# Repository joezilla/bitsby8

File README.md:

# BitsBy8

**BitsBy8** turns a Raspberry Pi (or any Linux/macOS machine) into a disk server and virtual-machine workbench for the **MITS Altair 8800** and other **S-100** computers.

It serves virtual floppy and hard-disk images to a real Altair through its **FDC+ Enhanced Floppy Disk Controller** over a serial cable — and it can also build and boot fully **virtual S-100 machines** right in your browser, no hardware required. Everything runs from a single Svelte web UI, with a REST API and an MCP server for AI assistants on the side.

**Version:** 3.0.0-alpha · **License:** GPL-3.0 · **Platforms:** Linux (Raspberry Pi & x86), macOS

---

## What it does

**Serve disks to a real Altair.** Mount up to four floppies (plus larger hard-disk images) and serve them to an unmodified Altair 8800 through its FDC+ controller over serial — or over a WebSocket link to an Altair *simulator*. Drives can be read-only or copy-on-write, and multiple machines can share the same library at once.

**Run virtual machines.** Assemble an S-100 computer from a catalog of emulated cards — CPU (8080/Z80), RAM, disk, serial, video — save it as a reusable **Machine Profile**, and boot it in the browser. Each running machine gets a live serial console, an Altair-style **front panel**, and a **video monitor** (VDM-1 character display / Cromemco Dazzler graphics). Snapshot a machine and restore it later.

**One place to drive it all.** The web UI, a full REST API, and an MCP server (90+ tools) all reach the same live state, so you can operate BitsBy8 by hand, from scripts, or from an AI assistant.

At a glance:

- 💾 **Disk serving** over real serial or WebSocket, with read-only and copy-on-write (transient / per-client "splinter") mounts you can keep, commit, or save as a new image
- 🖥️ **Virtual S-100 machines** — card catalog, machine profiles, and a run cockpit with console, front panel, and video monitor
- ⌨️ **VT102 terminal** in the browser for a real serial console or a virtual machine's console — reconnects where you left off
- 🧑‍🤝‍🧑 **Multi-client serving** so several machines (real and virtual) share one disk library
- 📼 **Cassette audio** playback
- 🤖 **AI assistant integration** via MCP (stdio or HTTP), plus OpenAPI/Swagger docs at `/api/docs`

---

## Quick start (no hardware needed)

Try the whole thing on your laptop — mount a sample disk or boot a virtual machine without an Altair in sight:

```bash
git clone <repo-url> fdcplus-web && cd fdcplus-web
pnpm install            # provisions the backend + frontend workspace
pnpm dev:all            # backend + web UI, live-reloading
open http://localhost:3000
```

Requires **Node.js 22+** and **pnpm**.

---

## Installation

### Raspberry Pi / Debian (recommended for real hardware)

Build and install the `.deb`, then run it as a systemd service:

```bash
make deb
sudo dpkg -i ../bitsby8_*.deb
sudo apt-get install -f            # pull in any missing dependencies

sudo nano /etc/bitsby8/bitsby8.config.json   # set your serial port, drives, etc.
sudo systemctl enable --now bitsby8          # start on boot and now
```

Upgrading from an older `fdcsds` install is automatic — apt supersedes it and
your config, data, and database are migrated. 

The web UI is then at `http://<pi-hostname>:3000`. See [DEBIAN-PACKAGE.md](DEBIAN-PACKAGE.md) for the full packaging guide.

### Docker

```bash
docker compose up -d      # then open the web UI (default port 3000)
```

Configuration and data persist in the mounted volume; see [`docker-compose.yml`](docker-compose.yml).

### From source

```bash
git clone <repo-url> fdcplus-web && cd fdcplus-web
pnpm install
pnpm build:all            # compile backend + build the web UI
pnpm start -- --web       # or: bitsby8 --web  (if installed globally)
```

---

## Connecting a real Altair

Wire the FDC+ controller to a USB serial adapter and point BitsBy8 at that port:

```bash
bitsby8 -p /dev/ttyUSB0 -0 disks/cpm22.dsk -w
# -p  serial port for the FDC+     -0..-3  mount a disk to a drive
# -w  enable the web interface     -b <rate>  set baud (default 230400)
```

A second serial port can drive an interactive **console terminal** in the web UI:

```bash
bitsby8 -p /dev/ttyUSB0 -0 disks/cpm22.dsk \
  --terminal-port /dev/ttyUSB1 --terminal-baud 9600 -w
```

A few setup notes:

- **Serial permissions (Linux):** add your user to the `dialout` group (`sudo usermod -aG dialout $USER`, then log out and back in).
- **Stable port names:** USB port names like `/dev/ttyUSB0` can shuffle across reboots. Run `bitsby8 --show-persistent-paths` to get a stable `/dev/serial/by-id/...` path for your config.
- **No physical FDC+?** An Altair *simulator* can connect over WebSocket instead of serial — see [docs/WS-FDC-TRANSPORT.md](docs/WS-FDC-TRANSPORT.md).

Generate a starter config any time with `bitsby8 --example-config > .bitsby8.config`, and run `bitsby8 --help` for the full option list.

---

## The web interface

Open the UI and everything is in the left sidebar:

| Section | What it's for |
|---|---|
| **Disks** | Mount/unmount images across the four drive bays, toggle read-only, browse and upload the disk library, take snapshots |
| **Virtual Machines** | Boot machine profiles and drive them in the run cockpit — serial console, Altair front panel, video monitor |
| **Card Catalog** / **Machine Profiles** | Assemble S-100 machines from emulated cards and save them as reusable profiles |
| **Terminal** | A VT102 console for a real serial port or a running virtual machine |
| **Cassettes** | Play cassette-tape audio images |
| **Disk Clients** | See and manage the machines currently sharing your disks (multi-client serving) |
| **Scripts** | Replay canned input / XMODEM transfers to a machine |
| **Config** | Server settings — serial defaults, web/API, MCP |

More detail in [docs/WEB-INTERFACE.md](docs/WEB-INTERFACE.md).

---

## AI assistant integration (MCP)

BitsBy8 ships a [Model Context Protocol](https://modelcontextprotocol.io/) server exposing 90+ tools — mount disks, drive machines, read/write CP/M files, run the terminal — to assistants like Claude Code. It's **off by default**; opt in per transport:

- **Local (stdio):** point your assistant at `bitsby8 --mcp`:
  ```json
  { "mcpServers": { "bitsby8": { "command": "bitsby8", "args": ["--mcp", "--data-dir", "/path/to/data"] } } }
  ```
- **Over the LAN (HTTP):** set an API key, then enable MCP-over-HTTP in *Config → MCP server* (or `--mcp-http`). It requires a bearer token and is intended for trusted networks — put TLS in front if you expose it.

The tools can read and **write** disk images and send bytes to real hardware, so don't point an assistant at a production machine without meaning to.

---

## Configuration

Settings live at two layers:

- **Install-time defaults** — a config file (`/etc/bitsby8/bitsby8.config.json`, or `.bitsby8.config` from source) plus CLI flags. These set up the box; changes take effect on restart.
- **Day-to-day settings** — managed live from the web UI (and REST/MCP), stored in a SQLite database in the data directory. Per-image settings like notes, write policy, and snapshots live here and apply immediately.

The data directory (`/var/lib/bitsby8` on a `.deb` install) holds your disk library, uploads, cassettes, and the database.

---

## Documentation

- [DEBIAN-PACKAGE.md](DEBIAN-PACKAGE.md) — building and installing the Debian package
- [docs/WEB-INTERFACE.md](docs/WEB-INTERFACE.md) — web UI walkthrough
- [docs/WS-FDC-TRANSPORT.md](docs/WS-FDC-TRANSPORT.md) — WebSocket disk transport for simulators
- [docs/PROTOCOL.md](docs/PROTOCOL.md) — the FDC+ serial disk protocol
- [docs/TROUBLESHOOTING.md](docs/TROUBLESHOOTING.md) — common issues
- [CONTRIBUTING.md](CONTRIBUTING.md) — how to contribute

---

## License

GPL-3.0.

## Credits

- **BitsBy8 software** (disk server, web interface, virtual machines, MCP server): Joe Toppe, 2024–present.
- **FDC+ Enhanced Floppy Disk Controller hardware:** Mike Douglas / [deramp.com](http://www.deramp.com). BitsBy8 talks to that controller over serial; the hardware itself is a separate product.

See [AUTHORS](AUTHORS) for the full contributor list.

## References

- [FDC+ Hardware Documentation](http://www.deramp.com)
- [Altair 8800 (Wikipedia)](https://en.wikipedia.org/wiki/Altair_8800)
- [Node.js SerialPort](https://serialport.io/)

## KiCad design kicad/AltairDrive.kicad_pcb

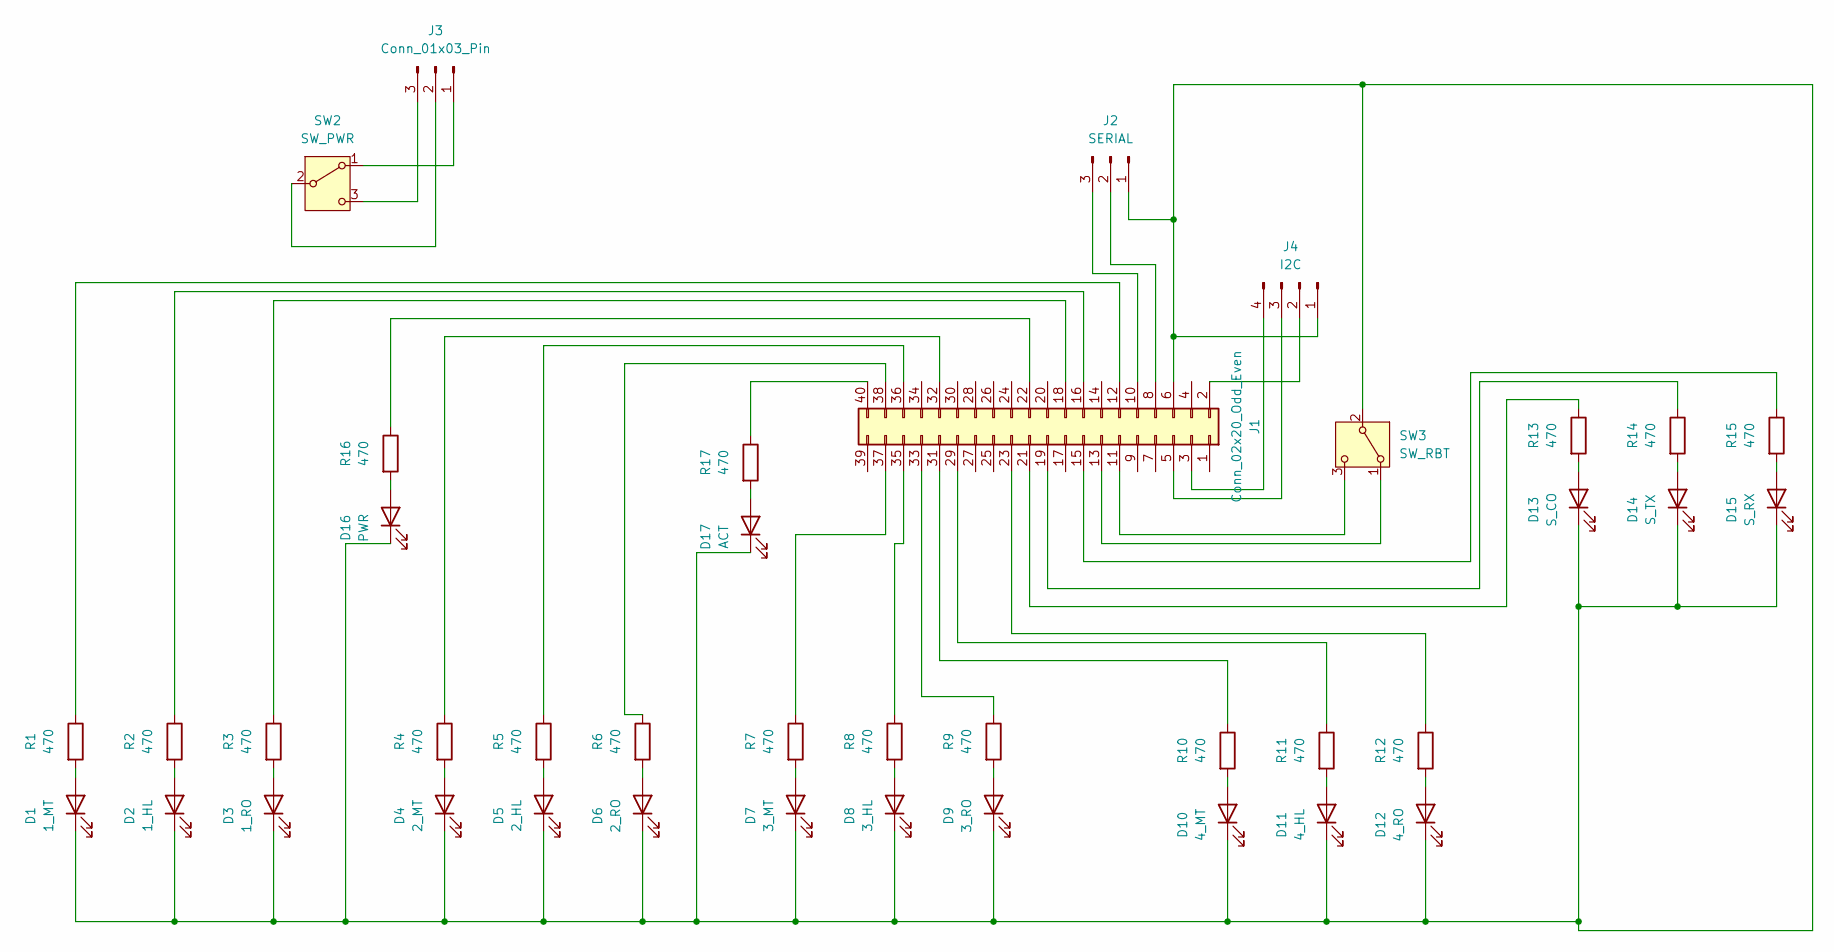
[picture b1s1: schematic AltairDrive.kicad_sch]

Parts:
D1: 1_MT; LED_D5.0mm
D2: 1_HL; LED_D5.0mm
D3: 1_RO; LED_D5.0mm
D4: 2_MT; LED_D5.0mm
D5: 2_HL; LED_D5.0mm
D6: 2_RO; LED_D5.0mm
D7: 3_MT; LED_D5.0mm
D8: 3_HL; LED_D5.0mm
D9: 3_RO; LED_D5.0mm
D10: 4_MT; LED_D5.0mm
D11: 4_HL; LED_D5.0mm
D12: 4_RO; LED_D5.0mm
D13: S_CO; LED_D5.0mm
D14: S_TX; LED_D5.0mm
D15: S_RX; LED_D5.0mm
D16: PWR; LED_D5.0mm
D17: ACT; LED_D5.0mm
J1: Conn_02x20_Odd_Even; PinHeader_2x20_P2.54mm_Vertical
J2: SERIAL; FanPinHeader_1x03_P2.54mm_Vertical
J3: Conn_01x03_Pin; FanPinHeader_1x03_P2.54mm_Vertical
J4: I2C; FanPinHeader_1x04_P2.54mm_Vertical
R1, R2, R3, R4, R5, R6, R7, R8, R9, R10, R11, R12, R13, R14, R15, R16, R17: 470; R_Bare_Metal_Element_L12.4mm_W4.8mm_P11.40mm
SW2: SW_PWR; E-Switch
SW3: SW_RBT; E-Switch

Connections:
unnamed: D1.2 (A), R1.2
unnamed: D1.1 (K), D2.1 (K), D3.1 (K), D4.1 (K), D5.1 (K), D6.1 (K), D7.1 (K), D8.1 (K), D9.1 (K), D10.1 (K), D11.1 (K), D12.1 (K), D13.1 (K), D14.1 (K), D15.1 (K), D16.1 (K), D17.1 (K), J1.6, J2.1, J4.1, SW3.2 (B)
unnamed: D2.2 (A), R2.2
unnamed: D3.2 (A), R3.2
unnamed: D4.2 (A), R4.2
unnamed: D5.2 (A), R5.2
unnamed: D6.2 (A), R6.2
unnamed: D7.2 (A), R7.2
unnamed: D8.2 (A), R8.2
unnamed: D9.2 (A), R9.2
unnamed: D10.2 (A), R10.2
unnamed: D11.2 (A), R11.2
unnamed: D12.2 (A), R12.2
unnamed: D13.2 (A), R13.2
unnamed: D14.2 (A), R14.2
unnamed: D15.2 (A), R15.2
unnamed: D16.2 (A), R16.2
unnamed: D17.2 (A), R17.2
unnamed: J1.2, J4.2
unnamed: J1.3, J4.4
unnamed: J1.5, J4.3
unnamed: J1.8, J2.2
unnamed: J1.10, J2.3
unnamed: J1.11, SW3.3 (C)
unnamed: J1.12, R1.1
unnamed: J1.13, SW3.1 (A)
unnamed: J1.15, R15.1
unnamed: J1.16, R2.1
unnamed: J1.18, R3.1
unnamed: J1.19, R14.1
unnamed: J1.21, R13.1
unnamed: J1.22, R16.1
unnamed: J1.23, R12.1
unnamed: J1.29, R11.1
unnamed: J1.31, R10.1
unnamed: J1.32, R4.1
unnamed: J1.33, R9.1
unnamed: J1.35, R8.1
unnamed: J1.36, R5.1
unnamed: J1.37, R7.1
unnamed: J1.38, R6.1
unnamed: J1.40, R17.1
unnamed: J3.1, SW2.1 (A)
unnamed: J3.2, SW2.2 (B)
unnamed: J3.3, SW2.3 (C)

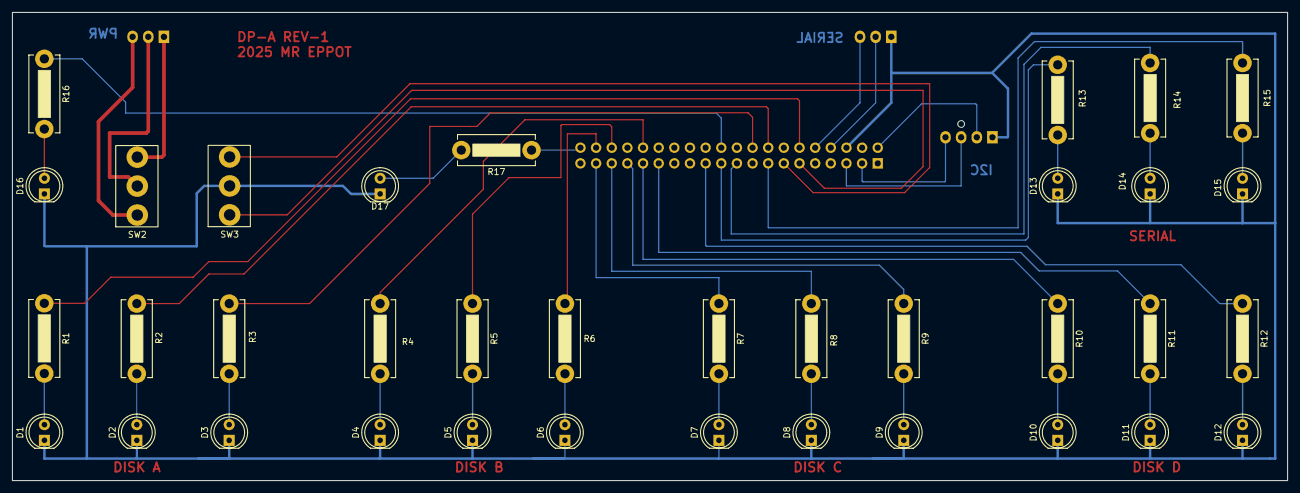
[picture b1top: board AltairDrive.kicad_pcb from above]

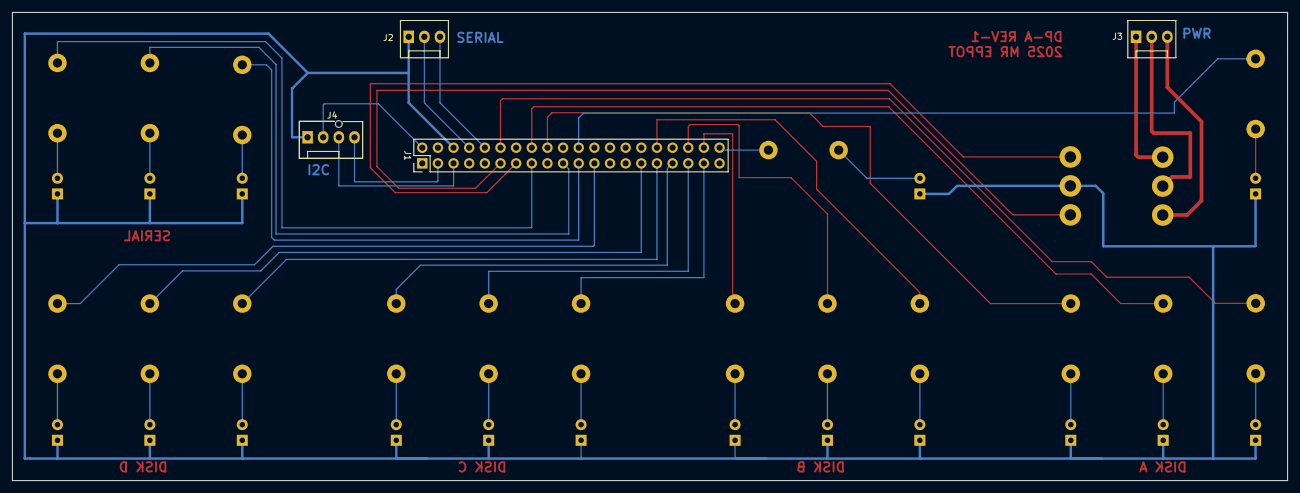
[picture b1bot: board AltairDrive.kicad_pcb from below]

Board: 2 copper layers, 207.0 x 76.0 mm, 40 parts (4 on the bottom side), 45 nets.

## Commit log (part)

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2025-11-17 one fix
2025-11-17 rename shell script
2025-11-17 add config samples
2025-11-17 nix the dist dir
2025-11-17 fixing a couple of little claude things
2025-11-17 raspberry pi fixes
2025-11-18 Update package-lock.json after removing lgpio
2025-11-21 snapshot
2025-11-25 kicad, progress
2025-11-28 kicad files for front panel
2025-11-28 logos
2025-11-29 fix package scripts to add gpio group
2025-12-19 missingfiles
2025-12-19 Fix script replay terminal connection error
    Replace undefined terminalSocket references with correct variables:
    - Use global terminalConnected boolean for connection checks
    - Use socket.emit('terminal:write') for sending commands (matches keyboard input)
    Fixes: ✗ Connection failed: terminalSocket is not defined
2025-12-19 persistent drive mapping
2025-12-19 fix socket issues on shutdown and add more config to web ui
2025-12-29 fix file handle cleanup
2025-12-29 fixes
2025-12-29 fix deps
2026-01-09 only log STAT in verbose mode
2026-01-16 crt mode
2026-01-19 config options for crt mode
2026-01-31 fix replay
2026-02-22 alternate command line client
2026-05-24 Correct authorship + attribution
    Two corrections rolled together.
    (1) Remove Patrick Linstruth from AUTHORS / Credits / Origins framing.
    This codebase is an independent TypeScript implementation that speaks
    the FDC+ wire protocol over serial — it talks to the same hardware,
    but Linstruth did not contribute to this software and the prior C
    codebase is not its source. Earlier README/AUTHORS copy implied a
2026-05-24 Fix Debian + Makefile build for pnpm workspace
    The pnpm migration deleted both lockfiles (root package-lock.json and
    frontend/package-lock.json), but debian/rules and Makefile were still
    calling `npm ci` and `npm install`. Reproduced: `make deb` fails at
    `cd frontend && npm ci` with EUSAGE (no package-lock.json).
    debian/rules now uses pnpm consistently:
    - `corepack enable pnpm` activates pnpm (bundled with Node 16+;
2026-05-24 Fix latent build errors surfaced by the Debian build
    Two real bugs that strict tsc on a clean Debian build host caught
    but my cached incremental build on macOS had been silently masking.
    1. zod was imported in src/mcp-server.ts but only present as a
    transitive of @modelcontextprotocol/sdk. pnpm's strict module
    resolution declines to expose transitives — the import worked
    locally only because pnpm's default hoisting on this machine
